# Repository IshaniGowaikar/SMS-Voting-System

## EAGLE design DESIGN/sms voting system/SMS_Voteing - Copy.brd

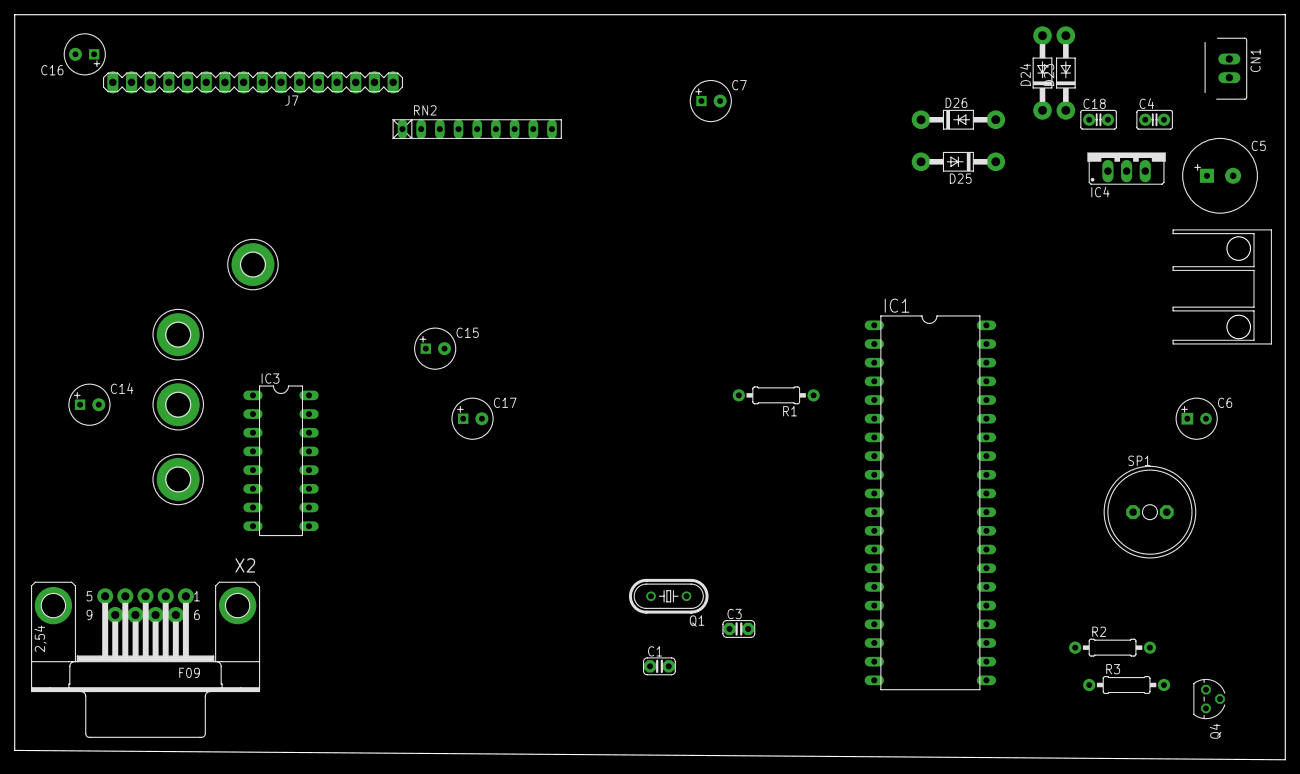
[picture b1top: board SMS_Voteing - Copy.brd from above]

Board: 2 copper layers, 172.7 x 101.3 mm, 33 parts (0 on the bottom side), 32 nets, no tracks yet.

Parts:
C1, C3: 33pF; C025-024X044
C4, C18: 0.1uF; C025-025X050
C5: 1000uF/25V; E3,5-10
C6: 220uF/16v; E2,5-6
C7, C14, C15, C16, C17: 1uF/16V; E2,5-6@1
CN1: JP2E; JP2
D23, D24, D25, D26: 1N4007; DO41-10
H1, H2, H3, H4: MOUNT-PAD-ROUND3.2; 3,2-PAD
HS3: HSD; HEATSINK
IC1: 89S52; DIL40
IC3: MAX232; DIL16
IC4: 7805; 78XXS
J7: 16 PIN MALE BURG; JP16
Q1: 11.0592MHz; HC49/S
Q4: BC547; TO92
R1, R2, R3: 1K; 0207/10
RN2: 10K; RN-9
SP1: BUZZER; AL11P
X2: F09HP

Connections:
+5V: C4.2, C6.+, C7.+, C15.-, C18.2, IC1.31, IC1.40, IC3.16, IC4.OUT, J7.2, J7.15, R2.2, RN2.1, SP1.+
+12V_R: C5.+, D23.C, D25.C, IC4.IN
GND: C1.1, C3.1, C4.1, C5.-, C6.-, C16.+, C18.1, D24.A, D26.A, IC1.20, IC3.15, IC4.GND, J7.1, J7.3, J7.16, Q4.1, R1.2, X2.5
unnamed: IC3.14, X2.2
unnamed: IC3.13, X2.3
unnamed: C14.+, IC3.1
unnamed: C14.-, IC3.3
unnamed: C17.+, IC3.4
unnamed: C17.-, IC3.5
unnamed: C15.+, IC3.2
unnamed: C16.-, IC3.6
unnamed: CN1.1, D25.A, D26.C
unnamed: C3.2, IC1.18, Q1.1
unnamed: C1.2, IC1.19, Q1.2
unnamed: Q4.2, R3.2
unnamed: Q4.3, SP1.-
unnamed: CN1.2, D23.A, D24.C
P0.0: IC1.39, J7.7, RN2.9
P0.1: IC1.38, J7.8, RN2.8
P0.2: IC1.37, J7.9, RN2.7
P0.3: IC1.36, J7.10, RN2.6
P0.4: IC1.35, J7.11, RN2.5
P0.5: IC1.34, J7.12, RN2.4
P0.6: IC1.33, J7.13, RN2.3
P0.7: IC1.32, J7.14, RN2.2
P2.4: IC1.25, R2.1, R3.1
P2.5: IC1.26, J7.4
P2.6: IC1.27, J7.5
P2.7: IC1.28, J7.6
P3.0: IC1.10, IC3.12
P3.1: IC1.11, IC3.11
RST: C7.-, IC1.9, R1.1

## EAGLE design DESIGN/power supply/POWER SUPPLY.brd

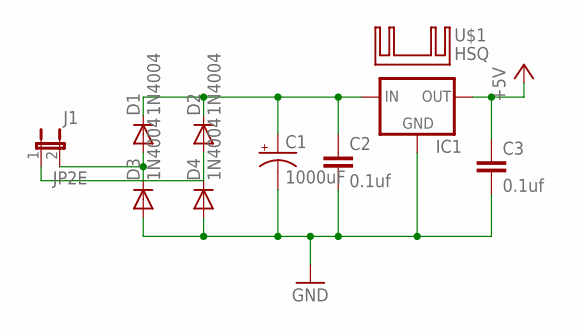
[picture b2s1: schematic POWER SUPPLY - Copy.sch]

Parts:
C1: 1000uF; E3,5-8
C2, C3: 0.1uf; C025-024X044
D1, D2, D3, D4: 1N4004; DO41-10
IC1: 78XXS
J1: JP2E; JP2
U$1: HSQ; HEATSINK

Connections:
+5V: C3.1, IC1.OUT
GND: C1.-, C2.2, C3.2, D3.A, D4.A, IC1.GND
unnamed: C1.+, C2.1, D1.C, D2.C, IC1.IN
unnamed: D1.A, D3.C, J1.2
unnamed: D2.A, D4.C, J1.1

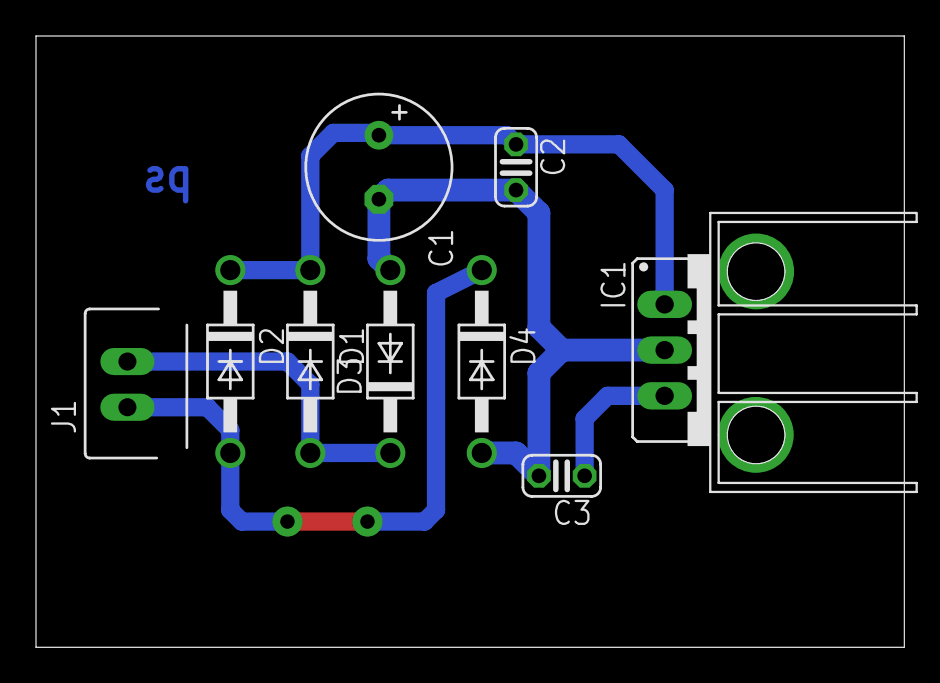
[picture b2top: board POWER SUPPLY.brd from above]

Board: 2 copper layers, 48.2 x 34.0 mm, 10 parts (0 on the bottom side), 5 nets.
